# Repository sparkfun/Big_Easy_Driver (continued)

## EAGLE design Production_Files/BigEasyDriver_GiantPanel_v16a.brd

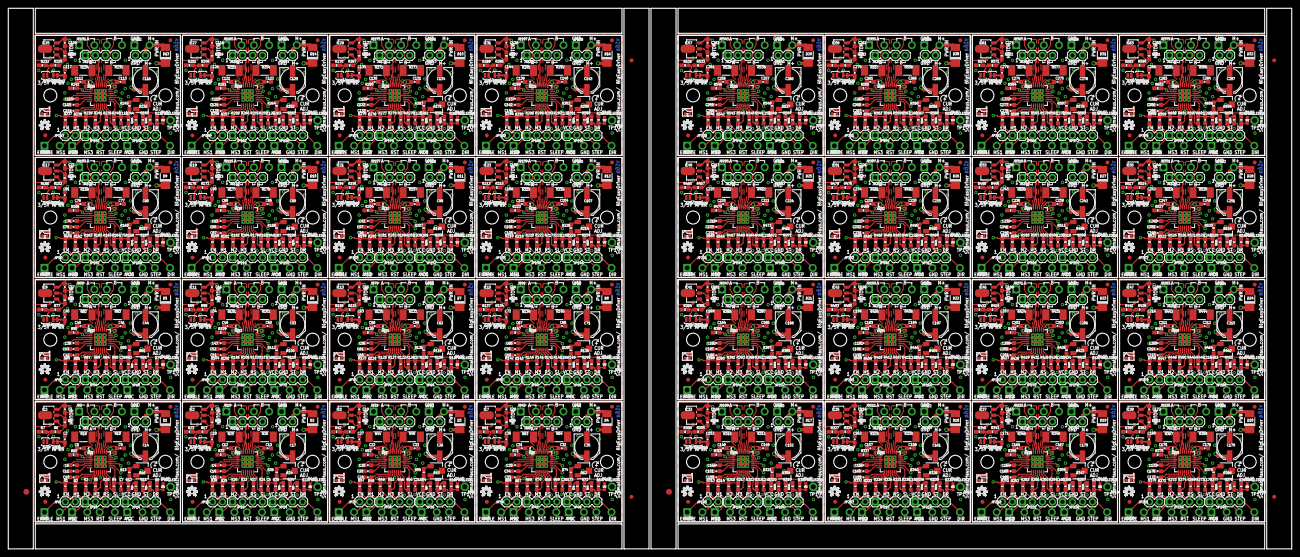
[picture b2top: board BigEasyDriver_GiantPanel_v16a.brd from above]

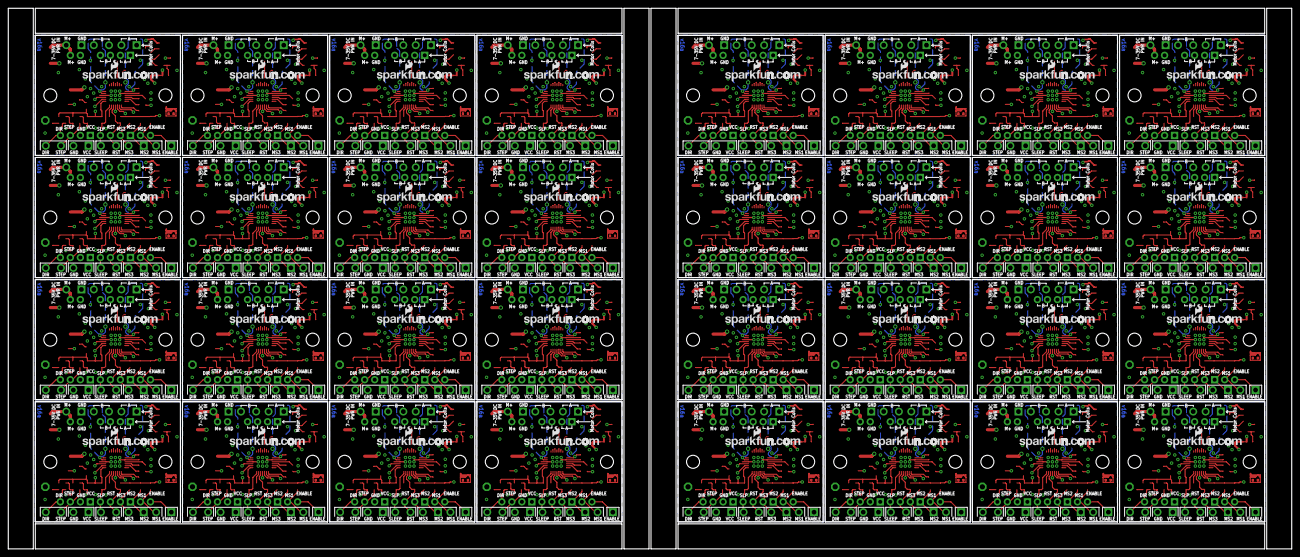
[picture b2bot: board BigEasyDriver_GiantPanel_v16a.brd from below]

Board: 4 copper layers, 325.6 x 137.2 mm, 1766 parts (32 on the bottom side), 1088 nets.

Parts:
3/5V, 3/5V1, 3/5V2, 3/5V3, 3/5V4, 3/5V5, 3/5V6, 3/5V7, 3/5V8, 3/5V9, 3/5V10, 3/5V11, 3/5V12, 3/5V13, 3/5V14, 3/5V15, 3/5V16, 3/5V17, 3/5V18, 3/5V19, 3/5V20, 3/5V21, 3/5V22, 3/5V23, 3/5V24, 3/5V25, 3/5V26, 3/5V27, 3/5V28, 3/5V29, 3/5V30, 3/5V31: SOLDERJUMPERNO; SJ_2S-NO
APWR, APWR1, APWR2, APWR3, APWR4, APWR5, APWR6, APWR7, APWR8, APWR9, APWR10, APWR11, APWR12, APWR13, APWR14, APWR15, APWR16, APWR17, APWR18, APWR19, APWR20, APWR21, APWR22, APWR23, APWR24, APWR25, APWR26, APWR27, APWR28, APWR29, APWR30, APWR31: SOLDERJUMPERTRACE; SJ_2S-TRACE
C1, C3, C19, C28, C37, C46, C55, C64, C73, C82, C91, C100, C109, C118, C127, C136, C145, C154, C163, C172, C181, C190, C199, C208, C217, C226, C235, C244, C253, C262, C271, C280: .1uF; 0603-CAP
C2, C18, C27, C36, C45, C54, C63, C72, C81, C90, C99, C108, C117, C126, C135, C144, C153, C162, C171, C180, C189, C198, C207, C216, C225, C234, C243, C252, C261, C270, C279, C288: 1uF; 0603-CAP
C4, C5, C6, C7, C8, C9, C11, C12, C13, C16, C20, C21, C22, C23, C25, C29, C30, C31, C32, C34, C38, C39, C40, C41, C43, C47, C48, C49, C50, C52, C56, C57, C58, C59, C61, C65, C66, C67, C68, C70, C74, C75, C76, C77, C79, C83, C84, C85, C86, C88, C92, C93, C94, C95, C97, C101, C102, C103, C104, C106, C110, C111, C112, C113, C115, C119, C120, C121, C122, C124, C128, C129, C130, C131, C133, C137, C138, C139, C140, C142, C146, C147, C148, C149, C151, C155, C156, C157, C158, C160, C164, C165, C166, C167, C169, C173, C174, C175, C176, C178, C182, C183, C184, C185, C187, C191, C192, C193, C194, C196, C200, C201, C202, C203, C205, C209, C210, C211, C212, C214, C218, C219, C220, C221, C223, C227, C228, C229, C230, C232, C236, C237, C238, C239, C241, C245, C246, C247, C248, C250, C254, C255, C256, C257, C259, C263, C264, C265, C266, C268, C272, C273, C274, C275, C277, C281, C282, C283, C284, C286: .1uf; 0603-CAP
C10, C15, C24, C33, C42, C51, C60, C69, C78, C87, C96, C105, C114, C123, C132, C141, C150, C159, C168, C177, C186, C195, C204, C213, C222, C231, C240, C249, C258, C267, C276, C285: .22uF; 0603-CAP
C14, C17, C26, C35, C44, C53, C62, C71, C80, C89, C98, C107, C116, C125, C134, C143, C152, C161, C170, C179, C188, C197, C206, C215, C224, C233, C242, C251, C260, C269, C278, C287: 47uF; PANASONIC_D
D1, D2, D3, D4, D5, D6, D7, D8, D9, D10, D11, D12, D13, D14, D15, D16, D17, D18, D19, D20, D21, D22, D23, D24, D25, D26, D27, D28, D29, D30, D31, D32: B340A-13-F; DO-214AC
E$1, E$4: FIDUCIAL-1.5X3
E$2, E$3, E$6, E$7: FIDUCIAL-1X2
FID1, FID2, FID3, FID4, FID5, FID6, FID7, FID8, FID9, FID10, FID11, FID12, FID13, FID14, FID15, FID16, FID17, FID18, FID19, FID20, FID21, FID22, FID23, FID24, FID25, FID26, FID27, FID28, FID29, FID30, FID31, FID32, FID33, FID34, FID35, FID36, FID37, FID38, FID39, FID40, FID41, FID42, FID43, FID44, FID45, FID46, FID47, FID48, FID49, FID50, FID51, FID52, FID53, FID54, FID55, FID56, FID57, FID58, FID59, FID60, FID61, FID62, FID63, FID64: FIDUCIAL1X2; FIDUCIAL-1X2
IC1, IC4, IC6, IC8, IC10, IC12, IC14, IC16, IC18, IC20, IC22, IC24, IC26, IC28, IC30, IC32, IC34, IC36, IC38, IC40, IC42, IC44, IC46, IC48, IC50, IC52, IC54, IC56, IC58, IC60, IC62, IC64: A4983ALT1; QFN-28-5MM_ALT1
IC2, IC3, IC5, IC7, IC9, IC11, IC13, IC15, IC17, IC19, IC21, IC23, IC25, IC27, IC29, IC31, IC33, IC35, IC37, IC39, IC41, IC43, IC45, IC47, IC49, IC51, IC53, IC55, IC57, IC59, IC61, IC63: LM317L; SCHMALZHAUS_SOT89
JP1, JP6, JP15, JP17, JP27, JP29, JP39, JP41, JP51, JP53, JP63, JP65, JP75, JP77, JP87, JP89, JP99, JP101, JP111, JP113, JP123, JP125, JP135, JP137, JP147, JP149, JP159, JP161, JP171, JP173, JP183, JP185, JP195, JP197, JP207, JP209, JP219, JP221, JP231, JP233, JP243, JP245, JP255, JP257, JP267, JP269, JP279, JP281, JP291, JP293, JP303, JP305, JP315, JP317, JP327, JP329, JP339, JP341, JP351, JP353, JP363, JP365, JP375, JP377: 1X02
JP2, JP4, JP8, JP9, JP25, JP26, JP37, JP38, JP49, JP50, JP61, JP62, JP73, JP74, JP85, JP86, JP97, JP98, JP109, JP110, JP121, JP122, JP133, JP134, JP145, JP146, JP157, JP158, JP169, JP170, JP181, JP182, JP193, JP194, JP205, JP206, JP217, JP218, JP229, JP230, JP241, JP242, JP253, JP254, JP265, JP266, JP277, JP278, JP289, JP290, JP301, JP302, JP313, JP314, JP325, JP326, JP337, JP338, JP349, JP350, JP361, JP362, JP373, JP374: STAND-OFF
JP3, JP10, JP14, JP16, JP18, JP24, JP28, JP30, JP36, JP40, JP42, JP48, JP52, JP54, JP60, JP64, JP66, JP72, JP76, JP78, JP84, JP88, JP90, JP96, JP100, JP102, JP108, JP112, JP114, JP120, JP124, JP126, JP132, JP136, JP138, JP144, JP148, JP150, JP156, JP160, JP162, JP168, JP172, JP174, JP180, JP184, JP186, JP192, JP196, JP198, JP204, JP208, JP210, JP216, JP220, JP222, JP228, JP232, JP234, JP240, JP244, JP246, JP252, JP256, JP258, JP264, JP268, JP270, JP276, JP280, JP282, JP288, JP292, JP294, JP300, JP304, JP306, JP312, JP316, JP318, JP324, JP328, JP330, JP336, JP340, JP342, JP348, JP352, JP354, JP360, JP364, JP366, JP372, JP376, JP378, JP384: 1X04
JP5, JP11, JP12, JP19, JP21, JP22, JP31, JP33, JP34, JP43, JP45, JP46, JP55, JP57, JP58, JP67, JP69, JP70, JP79, JP81, JP82, JP91, JP93, JP94, JP103, JP105, JP106, JP115, JP117, JP118, JP127, JP129, JP130, JP139, JP141, JP142, JP151, JP153, JP154, JP163, JP165, JP166, JP175, JP177, JP178, JP187, JP189, JP190, JP199, JP201, JP202, JP211, JP213, JP214, JP223, JP225, JP226, JP235, JP237, JP238, JP247, JP249, JP250, JP259, JP261, JP262, JP271, JP273, JP274, JP283, JP285, JP286, JP295, JP297, JP298, JP307, JP309, JP310, JP319, JP321, JP322, JP331, JP333, JP334, JP343, JP345, JP346, JP355, JP357, JP358, JP367, JP369, JP370, JP379, JP381, JP382: SCREWTERMINAL-3.5MM-4_LOCK
JP7, JP13, JP20, JP23, JP32, JP35, JP44, JP47, JP56, JP59, JP68, JP71, JP80, JP83, JP92, JP95, JP104, JP107, JP116, JP119, JP128, JP131, JP140, JP143, JP152, JP155, JP164, JP167, JP176, JP179, JP188, JP191, JP200, JP203, JP212, JP215, JP224, JP227, JP236, JP239, JP248, JP251, JP260, JP263, JP272, JP275, JP284, JP287, JP296, JP299, JP308, JP311, JP320, JP323, JP332, JP335, JP344, JP347, JP356, JP359, JP368, JP371, JP380, JP383: SCREWTERMINAL-3.5MM-2_LOCK
LOGO1, LOGO2, LOGO3, LOGO4, LOGO5, LOGO6, LOGO7, LOGO8, LOGO9, LOGO10, LOGO11, LOGO12, LOGO13, LOGO14, LOGO15, LOGO16, LOGO17, LOGO18, LOGO19, LOGO20, LOGO21, LOGO22, LOGO23, LOGO24, LOGO25, LOGO26, LOGO27, LOGO28, LOGO29, LOGO30, LOGO31, LOGO32: OSHW_LOGO_FILLX0100-NT; OSHW_FILLX100_NOTEXT
PWR_LED, PWR_LED1, PWR_LED2, PWR_LED3, PWR_LED4, PWR_LED5, PWR_LED6, PWR_LED7, PWR_LED8, PWR_LED9, PWR_LED10, PWR_LED11, PWR_LED12, PWR_LED13, PWR_LED14, PWR_LED15, PWR_LED16, PWR_LED17, PWR_LED18, PWR_LED19, PWR_LED20, PWR_LED21, PWR_LED22, PWR_LED23, PWR_LED24, PWR_LED25, PWR_LED26, PWR_LED27, PWR_LED28, PWR_LED29, PWR_LED30, PWR_LED31: YELLOW; LED-0603
R1, R2, R3, R4, R5, R10, R11, R12, R20, R27, R28, R29, R30, R31, R32, R33, R34, R35, R46, R47, R48, R49, R50, R51, R52, R53, R54, R65, R66, R67, R68, R69, R70, R71, R72, R73, R84, R85, R86, R87, R88, R89, R90, R91, R92, R103, R104, R105, R106, R107, R108, R109, R110, R111, R122, R123, R124, R125, R126, R127, R128, R129, R130, R141, R142, R143, R144, R145, R146, R147, R148, R149, R160, R161, R162, R163, R164, R165, R166, R167, R168, R179, R180, R181, R182, R183, R184, R185, R186, R187, R198, R199, R200, R201, R202, R203, R204, R205, R206, R217, R218, R219, R220, R221, R222, R223, R224, R225, R236, R237, R238, R239, R240, R241, R242, R243, R244, R255, R256, R257, R258, R259, R260, R261, R262, R263, R274, R275, R276, R277, R278, R279, R280, R281, R282, R293, R294, R295, R296, R297, R298, R299, R300, R301, R312, R313, R314, R315, R316, R317, R318, R319, R320, R331, R332, R333, R334, R335, R336, R337, R338, R339, R350, R351, R352, R353, R354, R355, R356, R357, R358, R369, R370, R371, R372, R373, R374, R375, R376, R377, R388, R389, R390, R391, R392, R393, R394, R395, R396, R407, R408, R409, R410, R411, R412, R413, R414, R415, R426, R427, R428, R429, R430, R431, R432, R433, R434, R445, R446, R447, R448, R449, R450, R451, R452, R453, R464, R465, R466, R467, R468, R469, R470, R471, R472, R483, R484, R485, R486, R487, R488, R489, R490, R491, R502, R503, R504, R505, R506, R507, R508, R509, R510, R521, R522, R523, R524, R525, R526, R527, R528, R529, R540, R541, R542, R543, R544, R545, R546, R547, R548, R559, R560, R561, R562, R563, R564, R565, R566, R567, R578, R579, R580, R581, R582, R583, R584, R585, R586, R597, R598, R599, R600, R601, R602, R603, R604, R605: 20K; 0603-RES
R6, R17, R39, R58, R77, R96, R115, R134, R153, R172, R191, R210, R229, R248, R267, R286, R305, R324, R343, R362, R381, R400, R419, R438, R457, R476, R495, R514, R533, R552, R571, R590: 390; 0603-RES
R7, R23, R42, R61, R80, R99, R118, R137, R156, R175, R194, R213, R232, R251, R270, R289, R308, R327, R346, R365, R384, R403, R422, R441, R460, R479, R498, R517, R536, R555, R574, R593: 330; 0603-RES
R8, R21, R40, R59, R78, R97, R116, R135, R154, R173, R192, R211, R230, R249, R268, R287, R306, R325, R344, R363, R382, R401, R420, R439, R458, R477, R496, R515, R534, R553, R572, R591: 240; 0603-RES
R9, R14, R15, R22, R37, R38, R41, R56, R57, R60, R75, R76, R79, R94, R95, R98, R113, R114, R117, R132, R133, R136, R151, R152, R155, R170, R171, R174, R189, R190, R193, R208, R209, R212, R227, R228, R231, R246, R247, R250, R265, R266, R269, R284, R285, R288, R303, R304, R307, R322, R323, R326, R341, R342, R345, R360, R361, R364, R379, R380, R383, R398, R399, R402, R417, R418, R421, R436, R437, R440, R455, R456, R459, R474, R475, R478, R493, R494, R497, R512, R513, R516, R531, R532, R535, R550, R551, R554, R569, R570, R573, R588, R589, R592, R607, R608: 1K; 0603-RES
R13, R36, R55, R74, R93, R112, R131, R150, R169, R188, R207, R226, R245, R264, R283, R302, R321, R340, R359, R378, R397, R416, R435, R454, R473, R492, R511, R530, R549, R568, R587, R606: 8.2K; 0603-RES
R16, R24, R43, R62, R81, R100, R119, R138, R157, R176, R195, R214, R233, R252, R271, R290, R309, R328, R347, R366, R385, R404, R423, R442, R461, R480, R499, R518, R537, R556, R575, R594: 10K; TRIMPOT-3MM-2
R18, R19, R25, R26, R44, R45, R63, R64, R82, R83, R101, R102, R120, R121, R139, R140, R158, R159, R177, R178, R196, R197, R215, R216, R234, R235, R253, R254, R272, R273, R291, R292, R310, R311, R329, R330, R348, R349, R367, R368, R386, R387, R405, R406, R424, R425, R443, R444, R462, R463, R481, R482, R500, R501, R519, R520, R538, R539, R557, R558, R576, R577, R595, R596: .11; R2010
TP1, TP2, TP3, TP4, TP5, TP6, TP7, TP8, TP9, TP10, TP11, TP12, TP13, TP14, TP15, TP16, TP17, TP18, TP19, TP20, TP21, TP22, TP23, TP24, TP25, TP26, TP27, TP28, TP29, TP30, TP31, TP32: TPPAD1-13; P1-13
U$1, U$6, U$11, U$16, U$21, U$26, U$31, U$36, U$41, U$46, U$51, U$56, U$61, U$66, U$71, U$76, U$81, U$86, U$91, U$96, U$101, U$106, U$111, U$116, U$121, U$126, U$131, U$136, U$141, U$146, U$151, U$156: SCHMALZHAUS_SMALL
U$2, U$7, U$12, U$17, U$22, U$27, U$32, U$37, U$42, U$47, U$52, U$57, U$62, U$67, U$72, U$77, U$82, U$87, U$92, U$97, U$102, U$107, U$112, U$117, U$122, U$127, U$132, U$137, U$142, U$147, U$152, U$157: LOGO-SFENEW; SFE-NEW-WEBLOGO
U$3, U$4, U$5, U$8, U$9, U$10, U$13, U$14, U$15, U$18, U$19, U$20, U$23, U$24, U$25, U$28, U$29, U$30, U$33, U$34, U$35, U$38, U$39, U$40, U$43, U$44, U$45, U$48, U$49, U$50, U$53, U$54, U$55, U$58, U$59, U$60, U$63, U$64, U$65, U$68, U$69, U$70, U$73, U$74, U$75, U$78, U$79, U$80, U$83, U$84, U$85, U$88, U$89, U$90, U$93, U$94, U$95, U$98, U$99, U$100, U$103, U$104, U$105, U$108, U$109, U$110, U$113, U$114, U$115, U$118, U$119, U$120, U$123, U$124, U$125, U$128, U$129, U$130, U$133, U$134, U$135, U$138, U$139, U$140, U$143, U$144, U$145, U$148, U$149, U$150, U$153, U$154, U$155, U$158, U$159, U$160: PAD; PAD-0.008

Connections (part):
5V_ALT: APWR.1, IC2.OUT, IC2.OUT@1, R8.2
5V_ALT1: APWR1.1, IC3.OUT, IC3.OUT@1, R21.2
5V_ALT2: APWR2.1, IC5.OUT, IC5.OUT@1, R40.2
5V_ALT3: APWR3.1, IC7.OUT, IC7.OUT@1, R59.2
5V_ALT4: APWR4.1, IC9.OUT, IC9.OUT@1, R78.2
5V_ALT5: APWR5.1, IC11.OUT, IC11.OUT@1, R97.2
5V_ALT6: APWR6.1, IC13.OUT, IC13.OUT@1, R116.2
5V_ALT7: APWR7.1, IC15.OUT, IC15.OUT@1, R135.2
5V_ALT8: APWR8.1, IC17.OUT, IC17.OUT@1, R154.2
5V_ALT9: APWR9.1, IC19.OUT, IC19.OUT@1, R173.2
5V_ALT10: APWR10.1, IC21.OUT, IC21.OUT@1, R192.2
5V_ALT11: APWR11.1, IC23.OUT, IC23.OUT@1, R211.2
5V_ALT12: APWR12.1, IC25.OUT, IC25.OUT@1, R230.2
5V_ALT13: APWR13.1, IC27.OUT, IC27.OUT@1, R249.2
5V_ALT14: APWR14.1, IC29.OUT, IC29.OUT@1, R268.2
5V_ALT15: APWR15.1, IC31.OUT, IC31.OUT@1, R287.2
5V_ALT16: APWR16.1, IC33.OUT, IC33.OUT@1, R306.2
5V_ALT17: APWR17.1, IC35.OUT, IC35.OUT@1, R325.2
5V_ALT18: APWR18.1, IC37.OUT, IC37.OUT@1, R344.2
5V_ALT19: APWR19.1, IC39.OUT, IC39.OUT@1, R363.2
5V_ALT20: APWR20.1, IC41.OUT, IC41.OUT@1, R382.2
5V_ALT21: APWR21.1, IC43.OUT, IC43.OUT@1, R401.2
5V_ALT22: APWR22.1, IC45.OUT, IC45.OUT@1, R420.2
5V_ALT23: APWR23.1, IC47.OUT, IC47.OUT@1, R439.2
5V_ALT24: APWR24.1, IC49.OUT, IC49.OUT@1, R458.2
5V_ALT25: APWR25.1, IC51.OUT, IC51.OUT@1, R477.2
5V_ALT26: APWR26.1, IC53.OUT, IC53.OUT@1, R496.2
5V_ALT27: APWR27.1, IC55.OUT, IC55.OUT@1, R515.2
5V_ALT28: APWR28.1, IC57.OUT, IC57.OUT@1, R534.2
5V_ALT29: APWR29.1, IC59.OUT, IC59.OUT@1, R553.2
5V_ALT30: APWR30.1, IC61.OUT, IC61.OUT@1, R572.2
5V_ALT31: APWR31.1, IC63.OUT, IC63.OUT@1, R591.2
COILA+: IC1.P$21, JP3.4, JP5.4
COILA+1: IC4.P$21, JP16.4, JP19.4
COILA+2: IC6.P$21, JP28.4, JP31.4
COILA+3: IC8.P$21, JP40.4, JP43.4
COILA+4: IC10.P$21, JP52.4, JP55.4
COILA+5: IC12.P$21, JP64.4, JP67.4
COILA+6: IC14.P$21, JP76.4, JP79.4
COILA+7: IC16.P$21, JP88.4, JP91.4
COILA+8: IC18.P$21, JP100.4, JP103.4
COILA+9: IC20.P$21, JP112.4, JP115.4
COILA+10: IC22.P$21, JP124.4, JP127.4
COILA+11: IC24.P$21, JP136.4, JP139.4
COILA+12: IC26.P$21, JP148.4, JP151.4
COILA+13: IC28.P$21, JP160.4, JP163.4
COILA+14: IC30.P$21, JP172.4, JP175.4
COILA+15: IC32.P$21, JP184.4, JP187.4
COILA+16: IC34.P$21, JP196.4, JP199.4
COILA+17: IC36.P$21, JP208.4, JP211.4
COILA+18: IC38.P$21, JP220.4, JP223.4
COILA+19: IC40.P$21, JP232.4, JP235.4
COILA+20: IC42.P$21, JP244.4, JP247.4
COILA+21: IC44.P$21, JP256.4, JP259.4
COILA+22: IC46.P$21, JP268.4, JP271.4
COILA+23: IC48.P$21, JP280.4, JP283.4
COILA+24: IC50.P$21, JP292.4, JP295.4
COILA+25: IC52.P$21, JP304.4, JP307.4
COILA+26: IC54.P$21, JP316.4, JP319.4
COILA+27: IC56.P$21, JP328.4, JP331.4
COILA+28: IC58.P$21, JP340.4, JP343.4
COILA+29: IC60.P$21, JP352.4, JP355.4
COILA+30: IC62.P$21, JP364.4, JP367.4
COILA+31: IC64.P$21, JP376.4, JP379.4
COILA-: IC1.P$24, JP3.3, JP5.3
COILA-1: IC4.P$24, JP16.3, JP19.3
COILA-2: IC6.P$24, JP28.3, JP31.3
COILA-3: IC8.P$24, JP40.3, JP43.3
COILA-4: IC10.P$24, JP52.3, JP55.3
COILA-5: IC12.P$24, JP64.3, JP67.3
COILA-6: IC14.P$24, JP76.3, JP79.3
COILA-7: IC16.P$24, JP88.3, JP91.3
COILA-8: IC18.P$24, JP100.3, JP103.3
COILA-9: IC20.P$24, JP112.3, JP115.3
COILA-10: IC22.P$24, JP124.3, JP127.3
COILA-11: IC24.P$24, JP136.3, JP139.3
COILA-12: IC26.P$24, JP148.3, JP151.3
COILA-13: IC28.P$24, JP160.3, JP163.3
COILA-14: IC30.P$24, JP172.3, JP175.3
COILA-15: IC32.P$24, JP184.3, JP187.3
COILA-16: IC34.P$24, JP196.3, JP199.3
COILA-17: IC36.P$24, JP208.3, JP211.3
COILA-18: IC38.P$24, JP220.3, JP223.3
COILA-19: IC40.P$24, JP232.3, JP235.3
COILA-20: IC42.P$24, JP244.3, JP247.3
COILA-21: IC44.P$24, JP256.3, JP259.3
COILA-22: IC46.P$24, JP268.3, JP271.3
COILA-23: IC48.P$24, JP280.3, JP283.3
COILA-24: IC50.P$24, JP292.3, JP295.3
COILA-25: IC52.P$24, JP304.3, JP307.3
COILA-26: IC54.P$24, JP316.3, JP319.3
COILA-27: IC56.P$24, JP328.3, JP331.3
COILA-28: IC58.P$24, JP340.3, JP343.3
COILA-29: IC60.P$24, JP352.3, JP355.3
COILA-30: IC62.P$24, JP364.3, JP367.3
COILA-31: IC64.P$24, JP376.3, JP379.3
COILB+: IC1.P$1, JP3.1, JP5.1
COILB+1: IC4.P$1, JP16.1, JP19.1
COILB+2: IC6.P$1, JP28.1, JP31.1
COILB+3: IC8.P$1, JP40.1, JP43.1
COILB+4: IC10.P$1, JP52.1, JP55.1
COILB+5: IC12.P$1, JP64.1, JP67.1
COILB+6: IC14.P$1, JP76.1, JP79.1
COILB+7: IC16.P$1, JP88.1, JP91.1
COILB+8: IC18.P$1, JP100.1, JP103.1
COILB+9: IC20.P$1, JP112.1, JP115.1
COILB+10: IC22.P$1, JP124.1, JP127.1
COILB+11: IC24.P$1, JP136.1, JP139.1
COILB+12: IC26.P$1, JP148.1, JP151.1
COILB+13: IC28.P$1, JP160.1, JP163.1
COILB+14: IC30.P$1, JP172.1, JP175.1
COILB+15: IC32.P$1, JP184.1, JP187.1
COILB+16: IC34.P$1, JP196.1, JP199.1
COILB+17: IC36.P$1, JP208.1, JP211.1
COILB+18: IC38.P$1, JP220.1, JP223.1
COILB+19: IC40.P$1, JP232.1, JP235.1
COILB+20: IC42.P$1, JP244.1, JP247.1
COILB+21: IC44.P$1, JP256.1, JP259.1
COILB+22: IC46.P$1, JP268.1, JP271.1
COILB+23: IC48.P$1, JP280.1, JP283.1
COILB+24: IC50.P$1, JP292.1, JP295.1
COILB+25: IC52.P$1, JP304.1, JP307.1
COILB+26: IC54.P$1, JP316.1, JP319.1
COILB+27: IC56.P$1, JP328.1, JP331.1
COILB+28: IC58.P$1, JP340.1, JP343.1
COILB+29: IC60.P$1, JP352.1, JP355.1
COILB+30: IC62.P$1, JP364.1, JP367.1
COILB+31: IC64.P$1, JP376.1, JP379.1
COILB-: IC1.P$26, JP3.2, JP5.2
COILB-1: IC4.P$26, JP16.2, JP19.2
COILB-2: IC6.P$26, JP28.2, JP31.2
COILB-3: IC8.P$26, JP40.2, JP43.2
COILB-4: IC10.P$26, JP52.2, JP55.2
COILB-5: IC12.P$26, JP64.2, JP67.2
COILB-6: IC14.P$26, JP76.2, JP79.2
COILB-7: IC16.P$26, JP88.2, JP91.2
COILB-8: IC18.P$26, JP100.2, JP103.2
COILB-9: IC20.P$26, JP112.2, JP115.2
COILB-10: IC22.P$26, JP124.2, JP127.2
COILB-11: IC24.P$26, JP136.2, JP139.2
COILB-12: IC26.P$26, JP148.2, JP151.2
COILB-13: IC28.P$26, JP160.2, JP163.2
COILB-14: IC30.P$26, JP172.2, JP175.2
COILB-15: IC32.P$26, JP184.2, JP187.2
COILB-16: IC34.P$26, JP196.2, JP199.2
COILB-17: IC36.P$26, JP208.2, JP211.2
COILB-18: IC38.P$26, JP220.2, JP223.2
COILB-19: IC40.P$26, JP232.2, JP235.2
COILB-20: IC42.P$26, JP244.2, JP247.2
COILB-21: IC44.P$26, JP256.2, JP259.2
COILB-22: IC46.P$26, JP268.2, JP271.2
COILB-23: IC48.P$26, JP280.2, JP283.2
COILB-24: IC50.P$26, JP292.2, JP295.2
COILB-25: IC52.P$26, JP304.2, JP307.2
COILB-26: IC54.P$26, JP316.2, JP319.2
COILB-27: IC56.P$26, JP328.2, JP331.2
COILB-28: IC58.P$26, JP340.2, JP343.2
COILB-29: IC60.P$26, JP352.2, JP355.2
COILB-30: IC62.P$26, JP364.2, JP367.2
COILB-31: IC64.P$26, JP376.2, JP379.2
CUR_REF: IC1.P$17, R16.2, TP1.TP
CUR_REF1: IC4.P$17, R24.2, TP2.TP
CUR_REF2: IC6.P$17, R43.2, TP3.TP
CUR_REF3: IC8.P$17, R62.2, TP4.TP
CUR_REF4: IC10.P$17, R81.2, TP5.TP
CUR_REF5: IC12.P$17, R100.2, TP6.TP
CUR_REF6: IC14.P$17, R119.2, TP7.TP
CUR_REF7: IC16.P$17, R138.2, TP8.TP
CUR_REF8: IC18.P$17, R157.2, TP9.TP
CUR_REF9: IC20.P$17, R176.2, TP10.TP
CUR_REF10: IC22.P$17, R195.2, TP11.TP
CUR_REF11: IC24.P$17, R214.2, TP12.TP
CUR_REF12: IC26.P$17, R233.2, TP13.TP
CUR_REF13: IC28.P$17, R252.2, TP14.TP
CUR_REF14: IC30.P$17, R271.2, TP15.TP
CUR_REF15: IC32.P$17, R290.2, TP16.TP
CUR_REF16: IC34.P$17, R309.2, TP17.TP
CUR_REF17: IC36.P$17, R328.2, TP18.TP
CUR_REF18: IC38.P$17, R347.2, TP19.TP
CUR_REF19: IC40.P$17, R366.2, TP20.TP
CUR_REF20: IC42.P$17, R385.2, TP21.TP
CUR_REF21: IC44.P$17, R404.2, TP22.TP
CUR_REF22: IC46.P$17, R423.2, TP23.TP
CUR_REF23: IC48.P$17, R442.2, TP24.TP
CUR_REF24: IC50.P$17, R461.2, TP25.TP
CUR_REF25: IC52.P$17, R480.2, TP26.TP
CUR_REF26: IC54.P$17, R499.2, TP27.TP
CUR_REF27: IC56.P$17, R518.2, TP28.TP
CUR_REF28: IC58.P$17, R537.2, TP29.TP
CUR_REF29: IC60.P$17, R556.2, TP30.TP
CUR_REF30: IC62.P$17, R575.2, TP31.TP
CUR_REF31: IC64.P$17, R594.2, TP32.TP
DIR: IC1.P$19, R11.1, R14.2
DIR1: IC4.P$19, R34.1, R37.2
DIR2: IC6.P$19, R53.1, R56.2
DIR3: IC8.P$19, R72.1, R75.2
DIR4: IC10.P$19, R91.1, R94.2
DIR5: IC12.P$19, R110.1, R113.2
DIR6: IC14.P$19, R129.1, R132.2
DIR7: IC16.P$19, R148.1, R151.2
DIR8: IC18.P$19, R167.1, R170.2
DIR9: IC20.P$19, R186.1, R189.2
DIR10: IC22.P$19, R205.1, R208.2
DIR11: IC24.P$19, R224.1, R227.2
DIR12: IC26.P$19, R243.1, R246.2
DIR13: IC28.P$19, R262.1, R265.2
DIR14: IC30.P$19, R281.1, R284.2
DIR15: IC32.P$19, R300.1, R303.2
DIR16: IC34.P$19, R319.1, R322.2
DIR17: IC36.P$19, R338.1, R341.2
DIR18: IC38.P$19, R357.1, R360.2
DIR19: IC40.P$19, R376.1, R379.2
DIR20: IC42.P$19, R395.1, R398.2
DIR21: IC44.P$19, R414.1, R417.2
DIR22: IC46.P$19, R433.1, R436.2
DIR23: IC48.P$19, R452.1, R455.2
DIR24: IC50.P$19, R471.1, R474.2
DIR25: IC52.P$19, R490.1, R493.2
DIR26: IC54.P$19, R509.1, R512.2
DIR27: IC56.P$19, R528.1, R531.2
DIR28: IC58.P$19, R547.1, R550.2
DIR29: IC60.P$19, R566.1, R569.2
DIR30: IC62.P$19, R585.1, R588.2
DIR31: IC64.P$19, R604.1, R607.2
DIR_IN: JP12.4, JP14.4, R14.1
DIR_IN1: JP22.4, JP24.4, R37.1
DIR_IN2: JP34.4, JP36.4, R56.1
DIR_IN3: JP46.4, JP48.4, R75.1
DIR_IN4: JP58.4, JP60.4, R94.1
DIR_IN5: JP70.4, JP72.4, R113.1
DIR_IN6: JP82.4, JP84.4, R132.1
DIR_IN7: JP94.4, JP96.4, R151.1
DIR_IN8: JP106.4, JP108.4, R170.1
DIR_IN9: JP118.4, JP120.4, R189.1
DIR_IN10: JP130.4, JP132.4, R208.1
DIR_IN11: JP142.4, JP144.4, R227.1
DIR_IN12: JP154.4, JP156.4, R246.1
DIR_IN13: JP166.4, JP168.4, R265.1
DIR_IN14: JP178.4, JP180.4, R284.1
DIR_IN15: JP190.4, JP192.4, R303.1
DIR_IN16: JP202.4, JP204.4, R322.1
DIR_IN17: JP214.4, JP216.4, R341.1
DIR_IN18: JP226.4, JP228.4, R360.1
DIR_IN19: JP238.4, JP240.4, R379.1
DIR_IN20: JP250.4, JP252.4, R398.1
DIR_IN21: JP262.4, JP264.4, R417.1
DIR_IN22: JP274.4, JP276.4, R436.1
DIR_IN23: JP286.4, JP288.4, R455.1
DIR_IN24: JP298.4, JP300.4, R474.1
DIR_IN25: JP310.4, JP312.4, R493.1
DIR_IN26: JP322.4, JP324.4, R512.1
DIR_IN27: JP334.4, JP336.4, R531.1
DIR_IN28: JP346.4, JP348.4, R550.1
DIR_IN29: JP358.4, JP360.4, R569.1
DIR_IN30: JP370.4, JP372.4, R588.1
DIR_IN31: JP382.4, JP384.4, R607.1
ENABLE: IC1.P$2, JP6.1, JP13.1, R10.1
ENABLE1: IC4.P$2, JP15.1, JP23.1, R33.1
ENABLE2: IC6.P$2, JP27.1, JP35.1, R52.1
ENABLE3: IC8.P$2, JP39.1, JP47.1, R71.1
ENABLE4: IC10.P$2, JP51.1, JP59.1, R90.1
ENABLE5: IC12.P$2, JP63.1, JP71.1, R109.1
ENABLE6: IC14.P$2, JP75.1, JP83.1, R128.1
ENABLE7: IC16.P$2, JP87.1, JP95.1, R147.1
ENABLE8: IC18.P$2, JP99.1, JP107.1, R166.1
ENABLE9: IC20.P$2, JP111.1, JP119.1, R185.1
ENABLE10: IC22.P$2, JP123.1, JP131.1, R204.1
ENABLE11: IC24.P$2, JP135.1, JP143.1, R223.1
ENABLE12: IC26.P$2, JP147.1, JP155.1, R242.1
ENABLE13: IC28.P$2, JP159.1, JP167.1, R261.1
ENABLE14: IC30.P$2, JP171.1, JP179.1, R280.1
ENABLE15: IC32.P$2, JP183.1, JP191.1, R299.1
ENABLE16: IC34.P$2, JP195.1, JP203.1, R318.1
ENABLE17: IC36.P$2, JP207.1, JP215.1, R337.1
ENABLE18: IC38.P$2, JP219.1, JP227.1, R356.1
ENABLE19: IC40.P$2, JP231.1, JP239.1, R375.1
ENABLE20: IC42.P$2, JP243.1, JP251.1, R394.1
ENABLE21: IC44.P$2, JP255.1, JP263.1, R413.1
ENABLE22: IC46.P$2, JP267.1, JP275.1, R432.1
ENABLE23: IC48.P$2, JP279.1, JP287.1, R451.1
ENABLE24: IC50.P$2, JP291.1, JP299.1, R470.1
ENABLE25: IC52.P$2, JP303.1, JP311.1, R489.1
ENABLE26: IC54.P$2, JP315.1, JP323.1, R508.1
ENABLE27: IC56.P$2, JP327.1, JP335.1, R527.1
ENABLE28: IC58.P$2, JP339.1, JP347.1, R546.1
ENABLE29: IC60.P$2, JP351.1, JP359.1, R565.1
ENABLE30: IC62.P$2, JP363.1, JP371.1, R584.1
ENABLE31: IC64.P$2, JP375.1, JP383.1, R603.1
GND: 3/5V.2, C1.2, C2.2, C7.2, C8.2, C9.2, C10.2, C14.-, IC1.P$3, IC1.P$18, IC1.P$29, JP1.1, JP7.1, JP12.2, JP14.2, PWR_LED.C, R7.1, R10.2, R16.3, R18.1, R19.1, R20.2
GND1: 3/5V1.2, C3.2, C5.2, C12.2, C13.2, C15.2, C17.-, C18.2, IC4.P$3, IC4.P$18, IC4.P$29, JP17.1, JP20.1, JP22.2, JP24.2, PWR_LED1.C, R23.1, R24.3, R25.1, R26.1, R27.2, R33.2
GND2: 3/5V2.2, C19.2, C21.2, C22.2, C23.2, C24.2, C26.-, C27.2, IC6.P$3, IC6.P$18, IC6.P$29, JP29.1, JP32.1, JP34.2, JP36.2, PWR_LED2.C, R42.1, R43.3, R44.1, R45.1, R46.2, R52.2
GND3: 3/5V3.2, C28.2, C30.2, C31.2, C32.2, C33.2, C35.-, C36.2, IC8.P$3, IC8.P$18, IC8.P$29, JP41.1, JP44.1, JP46.2, JP48.2, PWR_LED3.C, R61.1, R62.3, R63.1, R64.1, R65.2, R71.2
GND4: 3/5V4.2, C37.2, C39.2, C40.2, C41.2, C42.2, C44.-, C45.2, IC10.P$3, IC10.P$18, IC10.P$29, JP53.1, JP56.1, JP58.2, JP60.2, PWR_LED4.C, R80.1, R81.3, R82.1, R83.1, R84.2, R90.2
GND5: 3/5V5.2, C46.2, C48.2, C49.2, C50.2, C51.2, C53.-, C54.2, IC12.P$3, IC12.P$18, IC12.P$29, JP65.1, JP68.1, JP70.2, JP72.2, PWR_LED5.C, R99.1, R100.3, R101.1, R102.1, R103.2, R109.2
GND6: 3/5V6.2, C55.2, C57.2, C58.2, C59.2, C60.2, C62.-, C63.2, IC14.P$3, IC14.P$18, IC14.P$29, JP77.1, JP80.1, JP82.2, JP84.2, PWR_LED6.C, R118.1, R119.3, R120.1, R121.1, R122.2, R128.2
GND7: 3/5V7.2, C64.2, C66.2, C67.2, C68.2, C69.2, C71.-, C72.2, IC16.P$3, IC16.P$18, IC16.P$29, JP89.1, JP92.1, JP94.2, JP96.2, PWR_LED7.C, R137.1, R138.3, R139.1, R140.1, R141.2, R147.2
GND8: 3/5V8.2, C73.2, C75.2, C76.2, C77.2, C78.2, C80.-, C81.2, IC18.P$3, IC18.P$18, IC18.P$29, JP101.1, JP104.1, JP106.2, JP108.2, PWR_LED8.C, R156.1, R157.3, R158.1, R159.1, R160.2, R166.2
GND9: 3/5V9.2, C82.2, C84.2, C85.2, C86.2, C87.2, C89.-, C90.2, IC20.P$3, IC20.P$18, IC20.P$29, JP113.1, JP116.1, JP118.2, JP120.2, PWR_LED9.C, R175.1, R176.3, R177.1, R178.1, R179.2, R185.2
GND10: 3/5V10.2, C91.2, C93.2, C94.2, C95.2, C96.2, C98.-, C99.2, IC22.P$3, IC22.P$18, IC22.P$29, JP125.1, JP128.1, JP130.2, JP132.2, PWR_LED10.C, R194.1, R195.3, R196.1, R197.1, R198.2, R204.2
GND11: 3/5V11.2, C100.2, C102.2, C103.2, C104.2, C105.2, C107.-, C108.2, IC24.P$3, IC24.P$18, IC24.P$29, JP137.1, JP140.1, JP142.2, JP144.2, PWR_LED11.C, R213.1, R214.3, R215.1, R216.1, R217.2, R223.2
GND12: 3/5V12.2, C109.2, C111.2, C112.2, C113.2, C114.2, C116.-, C117.2, IC26.P$3, IC26.P$18, IC26.P$29, JP149.1, JP152.1, JP154.2, JP156.2, PWR_LED12.C, R232.1, R233.3, R234.1, R235.1, R236.2, R242.2
GND13: 3/5V13.2, C118.2, C120.2, C121.2, C122.2, C123.2, C125.-, C126.2, IC28.P$3, IC28.P$18, IC28.P$29, JP161.1, JP164.1, JP166.2, JP168.2, PWR_LED13.C, R251.1, R252.3, R253.1, R254.1, R255.2, R261.2
GND14: 3/5V14.2, C127.2, C129.2, C130.2, C131.2, C132.2, C134.-, C135.2, IC30.P$3, IC30.P$18, IC30.P$29, JP173.1, JP176.1, JP178.2, JP180.2, PWR_LED14.C, R270.1, R271.3, R272.1, R273.1, R274.2, R280.2
GND15: 3/5V15.2, C136.2, C138.2, C139.2, C140.2, C141.2, C143.-, C144.2, IC32.P$3, IC32.P$18, IC32.P$29, JP185.1, JP188.1, JP190.2, JP192.2, PWR_LED15.C, R289.1, R290.3, R291.1, R292.1, R293.2, R299.2
GND16: 3/5V16.2, C145.2, C147.2, C148.2, C149.2, C150.2, C152.-, C153.2, IC34.P$3, IC34.P$18, IC34.P$29, JP197.1, JP200.1, JP202.2, JP204.2, PWR_LED16.C, R308.1, R309.3, R310.1, R311.1, R312.2, R318.2
GND17: 3/5V17.2, C154.2, C156.2, C157.2, C158.2, C159.2, C161.-, C162.2, IC36.P$3, IC36.P$18, IC36.P$29, JP209.1, JP212.1, JP214.2, JP216.2, PWR_LED17.C, R327.1, R328.3, R329.1, R330.1, R331.2, R337.2
GND18: 3/5V18.2, C163.2, C165.2, C166.2, C167.2, C168.2, C170.-, C171.2, IC38.P$3, IC38.P$18, IC38.P$29, JP221.1, JP224.1, JP226.2, JP228.2, PWR_LED18.C, R346.1, R347.3, R348.1, R349.1, R350.2, R356.2
GND19: 3/5V19.2, C172.2, C174.2, C175.2, C176.2, C177.2, C179.-, C180.2, IC40.P$3, IC40.P$18, IC40.P$29, JP233.1, JP236.1, JP238.2, JP240.2, PWR_LED19.C, R365.1, R366.3, R367.1, R368.1, R369.2, R375.2
GND20: 3/5V20.2, C181.2, C183.2, C184.2, C185.2, C186.2, C188.-, C189.2, IC42.P$3, IC42.P$18, IC42.P$29, JP245.1, JP248.1, JP250.2, JP252.2, PWR_LED20.C, R384.1, R385.3, R386.1, R387.1, R388.2, R394.2
GND21: 3/5V21.2, C190.2, C192.2, C193.2, C194.2, C195.2, C197.-, C198.2, IC44.P$3, IC44.P$18, IC44.P$29, JP257.1, JP260.1, JP262.2, JP264.2, PWR_LED21.C, R403.1, R404.3, R405.1, R406.1, R407.2, R413.2
GND22: 3/5V22.2, C199.2, C201.2, C202.2, C203.2, C204.2, C206.-, C207.2, IC46.P$3, IC46.P$18, IC46.P$29, JP269.1, JP272.1, JP274.2, JP276.2, PWR_LED22.C, R422.1, R423.3, R424.1, R425.1, R426.2, R432.2
GND23: 3/5V23.2, C208.2, C210.2, C211.2, C212.2, C213.2, C215.-, C216.2, IC48.P$3, IC48.P$18, IC48.P$29, JP281.1, JP284.1, JP286.2, JP288.2, PWR_LED23.C, R441.1, R442.3, R443.1, R444.1, R445.2, R451.2
GND24: 3/5V24.2, C217.2, C219.2, C220.2, C221.2, C222.2, C224.-, C225.2, IC50.P$3, IC50.P$18, IC50.P$29, JP293.1, JP296.1, JP298.2, JP300.2, PWR_LED24.C, R460.1, R461.3, R462.1, R463.1, R464.2, R470.2
GND25: 3/5V25.2, C226.2, C228.2, C229.2, C230.2, C231.2, C233.-, C234.2, IC52.P$3, IC52.P$18, IC52.P$29, JP305.1, JP308.1, JP310.2, JP312.2, PWR_LED25.C, R479.1, R480.3, R481.1, R482.1, R483.2, R489.2
GND26: 3/5V26.2, C235.2, C237.2, C238.2, C239.2, C240.2, C242.-, C243.2, IC54.P$3, IC54.P$18, IC54.P$29, JP317.1, JP320.1, JP322.2, JP324.2, PWR_LED26.C, R498.1, R499.3, R500.1, R501.1, R502.2, R508.2
GND27: 3/5V27.2, C244.2, C246.2, C247.2, C248.2, C249.2, C251.-, C252.2, IC56.P$3, IC56.P$18, IC56.P$29, JP329.1, JP332.1, JP334.2, JP336.2, PWR_LED27.C, R517.1, R518.3, R519.1, R520.1, R521.2, R527.2
GND28: 3/5V28.2, C253.2, C255.2, C256.2, C257.2, C258.2, C260.-, C261.2, IC58.P$3, IC58.P$18, IC58.P$29, JP341.1, JP344.1, JP346.2, JP348.2, PWR_LED28.C, R536.1, R537.3, R538.1, R539.1, R540.2, R546.2
GND29: 3/5V29.2, C262.2, C264.2, C265.2, C266.2, C267.2, C269.-, C270.2, IC60.P$3, IC60.P$18, IC60.P$29, JP353.1, JP356.1, JP358.2, JP360.2, PWR_LED29.C, R555.1, R556.3, R557.1, R558.1, R559.2, R565.2
GND30: 3/5V30.2, C271.2, C273.2, C274.2, C275.2, C276.2, C278.-, C279.2, IC62.P$3, IC62.P$18, IC62.P$29, JP365.1, JP368.1, JP370.2, JP372.2, PWR_LED30.C, R574.1, R575.3, R576.1, R577.1, R578.2, R584.2
GND31: 3/5V31.2, C280.2, C282.2, C283.2, C284.2, C285.2, C287.-, C288.2, IC64.P$3, IC64.P$18, IC64.P$29, JP377.1, JP380.1, JP382.2, JP384.2, PWR_LED31.C, R593.1, R594.3, R595.1, R596.1, R597.2, R603.2
MS1: IC1.P$9, JP6.2, JP13.2, R1.1
MS2: IC1.P$10, JP10.1, JP11.1, R2.1
MS3: IC1.P$11, JP10.2, JP11.2, R3.1
MS4: IC4.P$9, JP15.2, JP23.2, R28.1
MS5: IC4.P$10, JP18.1, JP21.1, R29.1
MS6: IC4.P$11, JP18.2, JP21.2, R30.1
MS7: IC6.P$9, JP27.2, JP35.2, R47.1
MS8: IC6.P$10, JP30.1, JP33.1, R48.1
MS9: IC6.P$11, JP30.2, JP33.2, R49.1
MS10: IC8.P$9, JP39.2, JP47.2, R66.1
MS11: IC8.P$10, JP42.1, JP45.1, R67.1
MS12: IC8.P$11, JP42.2, JP45.2, R68.1
MS13: IC10.P$9, JP51.2, JP59.2, R85.1
MS14: IC10.P$10, JP54.1, JP57.1, R86.1
MS15: IC10.P$11, JP54.2, JP57.2, R87.1
MS16: IC12.P$9, JP63.2, JP71.2, R104.1
MS17: IC12.P$10, JP66.1, JP69.1, R105.1
MS18: IC12.P$11, JP66.2, JP69.2, R106.1
MS19: IC14.P$9, JP75.2, JP83.2, R123.1
MS20: IC14.P$10, JP78.1, JP81.1, R124.1
MS21: IC14.P$11, JP78.2, JP81.2, R125.1
MS22: IC16.P$9, JP87.2, JP95.2, R142.1
MS23: IC16.P$10, JP90.1, JP93.1, R143.1
MS24: IC16.P$11, JP90.2, JP93.2, R144.1
MS25: IC18.P$9, JP99.2, JP107.2, R161.1
MS26: IC18.P$10, JP102.1, JP105.1, R162.1
MS27: IC18.P$11, JP102.2, JP105.2, R163.1
MS28: IC20.P$9, JP111.2, JP119.2, R180.1
MS29: IC20.P$10, JP114.1, JP117.1, R181.1
MS30: IC20.P$11, JP114.2, JP117.2, R182.1
MS31: IC22.P$9, JP123.2, JP131.2, R199.1
MS32: IC22.P$10, JP126.1, JP129.1, R200.1
MS33: IC22.P$11, JP126.2, JP129.2, R201.1
MS34: IC24.P$9, JP135.2, JP143.2, R218.1
MS35: IC24.P$10, JP138.1, JP141.1, R219.1
MS36: IC24.P$11, JP138.2, JP141.2, R220.1
MS37: IC26.P$9, JP147.2, JP155.2, R237.1
MS38: IC26.P$10, JP150.1, JP153.1, R238.1
MS39: IC26.P$11, JP150.2, JP153.2, R239.1
MS40: IC28.P$9, JP159.2, JP167.2, R256.1
MS41: IC28.P$10, JP162.1, JP165.1, R257.1
MS42: IC28.P$11, JP162.2, JP165.2, R258.1
MS43: IC30.P$9, JP171.2, JP179.2, R275.1
MS44: IC30.P$10, JP174.1, JP177.1, R276.1
MS45: IC30.P$11, JP174.2, JP177.2, R277.1
MS46: IC32.P$9, JP183.2, JP191.2, R294.1
MS47: IC32.P$10, JP186.1, JP189.1, R295.1
MS48: IC32.P$11, JP186.2, JP189.2, R296.1
MS49: IC34.P$9, JP195.2, JP203.2, R313.1
MS50: IC34.P$10, JP198.1, JP201.1, R314.1
MS51: IC34.P$11, JP198.2, JP201.2, R315.1
MS52: IC36.P$9, JP207.2, JP215.2, R332.1
MS53: IC36.P$10, JP210.1, JP213.1, R333.1
MS54: IC36.P$11, JP210.2, JP213.2, R334.1
MS55: IC38.P$9, JP219.2, JP227.2, R351.1
MS56: IC38.P$10, JP222.1, JP225.1, R352.1
MS57: IC38.P$11, JP222.2, JP225.2, R353.1
MS58: IC40.P$9, JP231.2, JP239.2, R370.1
MS59: IC40.P$10, JP234.1, JP237.1, R371.1
MS60: IC40.P$11, JP234.2, JP237.2, R372.1
MS61: IC42.P$9, JP243.2, JP251.2, R389.1
MS62: IC42.P$10, JP246.1, JP249.1, R390.1
MS63: IC42.P$11, JP246.2, JP249.2, R391.1
MS64: IC44.P$9, JP255.2, JP263.2, R408.1
MS65: IC44.P$10, JP258.1, JP261.1, R409.1
MS66: IC44.P$11, JP258.2, JP261.2, R410.1
MS67: IC46.P$9, JP267.2, JP275.2, R427.1
MS68: IC46.P$10, JP270.1, JP273.1, R428.1
MS69: IC46.P$11, JP270.2, JP273.2, R429.1
MS70: IC48.P$9, JP279.2, JP287.2, R446.1
MS71: IC48.P$10, JP282.1, JP285.1, R447.1
MS72: IC48.P$11, JP282.2, JP285.2, R448.1
MS73: IC50.P$9, JP291.2, JP299.2, R465.1
MS74: IC50.P$10, JP294.1, JP297.1, R466.1
MS75: IC50.P$11, JP294.2, JP297.2, R467.1
MS76: IC52.P$9, JP303.2, JP311.2, R484.1
MS77: IC52.P$10, JP306.1, JP309.1, R485.1
MS78: IC52.P$11, JP306.2, JP309.2, R486.1
MS79: IC54.P$9, JP315.2, JP323.2, R503.1
MS80: IC54.P$10, JP318.1, JP321.1, R504.1
MS81: IC54.P$11, JP318.2, JP321.2, R505.1
MS82: IC56.P$9, JP327.2, JP335.2, R522.1
MS83: IC56.P$10, JP330.1, JP333.1, R523.1
MS84: IC56.P$11, JP330.2, JP333.2, R524.1
MS85: IC58.P$9, JP339.2, JP347.2, R541.1
MS86: IC58.P$10, JP342.1, JP345.1, R542.1
MS87: IC58.P$11, JP342.2, JP345.2, R543.1
MS88: IC60.P$9, JP351.2, JP359.2, R560.1
MS89: IC60.P$10, JP354.1, JP357.1, R561.1
MS90: IC60.P$11, JP354.2, JP357.2, R562.1
MS91: IC62.P$9, JP363.2, JP371.2, R579.1
MS92: IC62.P$10, JP366.1, JP369.1, R580.1
MS93: IC62.P$11, JP366.2, JP369.2, R581.1
MS94: IC64.P$9, JP375.2, JP383.2, R598.1
MS95: IC64.P$10, JP378.1, JP381.1, R599.1
MS96: IC64.P$11, JP378.2, JP381.2, R600.1
unnamed: D1.A, JP1.2, JP7.2
unnamed: PWR_LED.A, R9.1
unnamed: R13.2, R16.1
unnamed: 3/5V.1, R6.1, R7.2
unnamed: IC1.P$7, U$3.P$1
unnamed: IC2.ADJ, R6.2, R8.1
unnamed: IC1.P$20, U$4.P$1
unnamed: C6.1, IC1.P$4
unnamed: C6.2, IC1.P$5
unnamed: IC1.P$25, U$5.P$1
unnamed: IC3.ADJ, R17.2, R21.1
unnamed: PWR_LED1.A, R22.1
unnamed: 3/5V1.1, R17.1, R23.2
unnamed: IC4.P$27, R25.2
unnamed: IC4.P$23, R26.2
unnamed: C4.1, IC4.P$4
unnamed: C4.2, IC4.P$5
unnamed: IC4.P$13, R27.1
unnamed: IC1.P$13, R20.1
unnamed: C10.1, IC1.P$8
unnamed: C11.1, IC1.P$6
unnamed: C15.1, IC4.P$8
unnamed: C16.1, IC4.P$6
unnamed: D2.A, JP17.2, JP20.2
unnamed: R24.1, R36.2
unnamed: IC4.P$7, U$8.P$1
unnamed: IC4.P$20, U$9.P$1
unnamed: IC4.P$25, U$10.P$1
unnamed: IC5.ADJ, R39.2, R40.1
unnamed: PWR_LED2.A, R41.1
unnamed: IC1.P$27, R18.2
unnamed: IC1.P$23, R19.2
unnamed: 3/5V2.1, R39.1, R42.2
unnamed: IC6.P$27, R44.2
unnamed: IC6.P$23, R45.2
unnamed: C20.1, IC6.P$4
unnamed: C20.2, IC6.P$5
unnamed: IC6.P$13, R46.1
unnamed: C24.1, IC6.P$8
unnamed: C25.1, IC6.P$6
unnamed: D3.A, JP29.2, JP32.2
unnamed: R43.1, R55.2
unnamed: IC6.P$7, U$13.P$1
unnamed: IC6.P$20, U$14.P$1
unnamed: IC6.P$25, U$15.P$1
unnamed: IC7.ADJ, R58.2, R59.1
unnamed: PWR_LED3.A, R60.1
unnamed: 3/5V3.1, R58.1, R61.2
unnamed: IC8.P$27, R63.2
unnamed: IC8.P$23, R64.2
unnamed: C29.1, IC8.P$4
unnamed: C29.2, IC8.P$5
unnamed: IC8.P$13, R65.1
unnamed: C33.1, IC8.P$8
unnamed: C34.1, IC8.P$6
unnamed: D4.A, JP41.2, JP44.2
unnamed: R62.1, R74.2
unnamed: IC8.P$7, U$18.P$1
unnamed: IC8.P$20, U$19.P$1
unnamed: IC8.P$25, U$20.P$1
unnamed: IC9.ADJ, R77.2, R78.1
unnamed: PWR_LED4.A, R79.1
unnamed: 3/5V4.1, R77.1, R80.2
unnamed: IC10.P$27, R82.2
unnamed: IC10.P$23, R83.2
unnamed: C38.1, IC10.P$4
unnamed: C38.2, IC10.P$5
unnamed: IC10.P$13, R84.1
unnamed: C42.1, IC10.P$8
unnamed: C43.1, IC10.P$6
unnamed: D5.A, JP53.2, JP56.2
unnamed: R81.1, R93.2
unnamed: IC10.P$7, U$23.P$1
unnamed: IC10.P$20, U$24.P$1
unnamed: IC10.P$25, U$25.P$1
unnamed: IC11.ADJ, R96.2, R97.1
unnamed: PWR_LED5.A, R98.1
unnamed: 3/5V5.1, R96.1, R99.2
unnamed: IC12.P$27, R101.2
unnamed: IC12.P$23, R102.2
unnamed: C47.1, IC12.P$4
unnamed: C47.2, IC12.P$5
unnamed: IC12.P$13, R103.1
unnamed: C51.1, IC12.P$8
unnamed: C52.1, IC12.P$6
unnamed: D6.A, JP65.2, JP68.2
unnamed: R100.1, R112.2
unnamed: IC12.P$7, U$28.P$1
unnamed: IC12.P$20, U$29.P$1
unnamed: IC12.P$25, U$30.P$1
unnamed: IC13.ADJ, R115.2, R116.1
unnamed: PWR_LED6.A, R117.1
unnamed: 3/5V6.1, R115.1, R118.2
unnamed: IC14.P$27, R120.2
unnamed: IC14.P$23, R121.2
unnamed: C56.1, IC14.P$4
unnamed: C56.2, IC14.P$5
unnamed: IC14.P$13, R122.1
unnamed: C60.1, IC14.P$8
unnamed: C61.1, IC14.P$6
unnamed: D7.A, JP77.2, JP80.2
unnamed: R119.1, R131.2
unnamed: IC14.P$7, U$33.P$1
unnamed: IC14.P$20, U$34.P$1
unnamed: IC14.P$25, U$35.P$1
unnamed: IC15.ADJ, R134.2, R135.1
unnamed: PWR_LED7.A, R136.1
unnamed: 3/5V7.1, R134.1, R137.2
unnamed: IC16.P$27, R139.2
unnamed: IC16.P$23, R140.2
unnamed: C65.1, IC16.P$4
unnamed: C65.2, IC16.P$5
unnamed: IC16.P$13, R141.1
unnamed: C69.1, IC16.P$8
unnamed: C70.1, IC16.P$6
unnamed: D8.A, JP89.2, JP92.2
unnamed: R138.1, R150.2
unnamed: IC16.P$7, U$38.P$1
unnamed: IC16.P$20, U$39.P$1
unnamed: IC16.P$25, U$40.P$1
unnamed: IC17.ADJ, R153.2, R154.1
unnamed: PWR_LED8.A, R155.1
unnamed: 3/5V8.1, R153.1, R156.2
unnamed: IC18.P$27, R158.2
unnamed: IC18.P$23, R159.2
unnamed: C74.1, IC18.P$4
unnamed: C74.2, IC18.P$5
unnamed: IC18.P$13, R160.1
unnamed: C78.1, IC18.P$8
unnamed: C79.1, IC18.P$6
unnamed: D9.A, JP101.2, JP104.2
unnamed: R157.1, R169.2
unnamed: IC18.P$7, U$43.P$1
unnamed: IC18.P$20, U$44.P$1
unnamed: IC18.P$25, U$45.P$1
unnamed: IC19.ADJ, R172.2, R173.1
unnamed: PWR_LED9.A, R174.1
unnamed: 3/5V9.1, R172.1, R175.2
unnamed: IC20.P$27, R177.2
unnamed: IC20.P$23, R178.2
unnamed: C83.1, IC20.P$4
unnamed: C83.2, IC20.P$5
unnamed: IC20.P$13, R179.1
unnamed: C87.1, IC20.P$8
unnamed: C88.1, IC20.P$6
unnamed: D10.A, JP113.2, JP116.2
unnamed: R176.1, R188.2
unnamed: IC20.P$7, U$48.P$1
unnamed: IC20.P$20, U$49.P$1
unnamed: IC20.P$25, U$50.P$1
unnamed: IC21.ADJ, R191.2, R192.1
unnamed: PWR_LED10.A, R193.1
unnamed: 3/5V10.1, R191.1, R194.2
unnamed: IC22.P$27, R196.2
unnamed: IC22.P$23, R197.2
unnamed: C92.1, IC22.P$4
unnamed: C92.2, IC22.P$5
unnamed: IC22.P$13, R198.1
unnamed: C96.1, IC22.P$8
unnamed: C97.1, IC22.P$6
unnamed: D11.A, JP125.2, JP128.2
unnamed: R195.1, R207.2
unnamed: IC22.P$7, U$53.P$1
unnamed: IC22.P$20, U$54.P$1
unnamed: IC22.P$25, U$55.P$1
unnamed: IC23.ADJ, R210.2, R211.1
unnamed: PWR_LED11.A, R212.1
unnamed: 3/5V11.1, R210.1, R213.2
unnamed: IC24.P$27, R215.2
unnamed: IC24.P$23, R216.2
unnamed: C101.1, IC24.P$4
unnamed: C101.2, IC24.P$5
unnamed: IC24.P$13, R217.1
unnamed: C105.1, IC24.P$8
unnamed: C106.1, IC24.P$6
unnamed: D12.A, JP137.2, JP140.2
unnamed: R214.1, R226.2
unnamed: IC24.P$7, U$58.P$1
unnamed: IC24.P$20, U$59.P$1
unnamed: IC24.P$25, U$60.P$1
unnamed: IC25.ADJ, R229.2, R230.1
unnamed: PWR_LED12.A, R231.1
unnamed: 3/5V12.1, R229.1, R232.2
unnamed: IC26.P$27, R234.2
unnamed: IC26.P$23, R235.2
unnamed: C110.1, IC26.P$4
unnamed: C110.2, IC26.P$5
unnamed: IC26.P$13, R236.1
unnamed: C114.1, IC26.P$8
unnamed: C115.1, IC26.P$6
unnamed: D13.A, JP149.2, JP152.2
unnamed: R233.1, R245.2
unnamed: IC26.P$7, U$63.P$1
unnamed: IC26.P$20, U$64.P$1
unnamed: IC26.P$25, U$65.P$1
unnamed: IC27.ADJ, R248.2, R249.1
unnamed: PWR_LED13.A, R250.1
unnamed: 3/5V13.1, R248.1, R251.2
unnamed: IC28.P$27, R253.2
unnamed: IC28.P$23, R254.2
unnamed: C119.1, IC28.P$4
unnamed: C119.2, IC28.P$5
unnamed: IC28.P$13, R255.1
unnamed: C123.1, IC28.P$8
unnamed: C124.1, IC28.P$6
unnamed: D14.A, JP161.2, JP164.2
unnamed: R252.1, R264.2
unnamed: IC28.P$7, U$68.P$1
unnamed: IC28.P$20, U$69.P$1
unnamed: IC28.P$25, U$70.P$1
unnamed: IC29.ADJ, R267.2, R268.1
unnamed: PWR_LED14.A, R269.1
unnamed: 3/5V14.1, R267.1, R270.2
unnamed: IC30.P$27, R272.2
unnamed: IC30.P$23, R273.2
unnamed: C128.1, IC30.P$4
unnamed: C128.2, IC30.P$5
unnamed: IC30.P$13, R274.1
unnamed: C132.1, IC30.P$8
unnamed: C133.1, IC30.P$6
unnamed: D15.A, JP173.2, JP176.2
unnamed: R271.1, R283.2
unnamed: IC30.P$7, U$73.P$1
unnamed: IC30.P$20, U$74.P$1
unnamed: IC30.P$25, U$75.P$1
unnamed: IC31.ADJ, R286.2, R287.1
unnamed: PWR_LED15.A, R288.1
unnamed: 3/5V15.1, R286.1, R289.2
unnamed: IC32.P$27, R291.2
unnamed: IC32.P$23, R292.2
unnamed: C137.1, IC32.P$4
unnamed: C137.2, IC32.P$5
unnamed: IC32.P$13, R293.1
unnamed: C141.1, IC32.P$8
unnamed: C142.1, IC32.P$6
unnamed: D16.A, JP185.2, JP188.2
unnamed: R290.1, R302.2
unnamed: IC32.P$7, U$78.P$1
unnamed: IC32.P$20, U$79.P$1
unnamed: IC32.P$25, U$80.P$1
unnamed: IC33.ADJ, R305.2, R306.1
unnamed: PWR_LED16.A, R307.1
unnamed: 3/5V16.1, R305.1, R308.2
unnamed: IC34.P$27, R310.2
unnamed: IC34.P$23, R311.2
unnamed: C146.1, IC34.P$4
unnamed: C146.2, IC34.P$5
unnamed: IC34.P$13, R312.1
unnamed: C150.1, IC34.P$8
unnamed: C151.1, IC34.P$6
unnamed: D17.A, JP197.2, JP200.2
unnamed: R309.1, R321.2
unnamed: IC34.P$7, U$83.P$1
unnamed: IC34.P$20, U$84.P$1
unnamed: IC34.P$25, U$85.P$1
unnamed: IC35.ADJ, R324.2, R325.1
unnamed: PWR_LED17.A, R326.1
unnamed: 3/5V17.1, R324.1, R327.2
unnamed: IC36.P$27, R329.2
unnamed: IC36.P$23, R330.2
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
